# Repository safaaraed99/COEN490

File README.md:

# COEN490 Hardware
This repository contains the PCB design files and AVR microcontroller firmware.

# Firmware contribution
First, install [Microchip Studio](https://www.microchip.com/en-us/tools-resources/develop/microchip-studio) (AKA Atmel Studio).

Next, create a new branch for the feature you want to add. Open up the solution under avr_firmware, make the modifications, commit and push to your branch. Then open up a PR and wait for a review before merging.

See `docs/main.md` for documentation links and programming guides.

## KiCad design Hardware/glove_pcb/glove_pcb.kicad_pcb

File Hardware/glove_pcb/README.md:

Hardware design for the project's PCB

1. Download [Kicad](https://www.kicad.org/) and open `glove_pcb.kicad_pro`
2. Modify schematic in `glove_pcb.kicad_sch`
3. Modify PCB layout in `glove_pcb.kicad_pcb`

TODO write more here!!

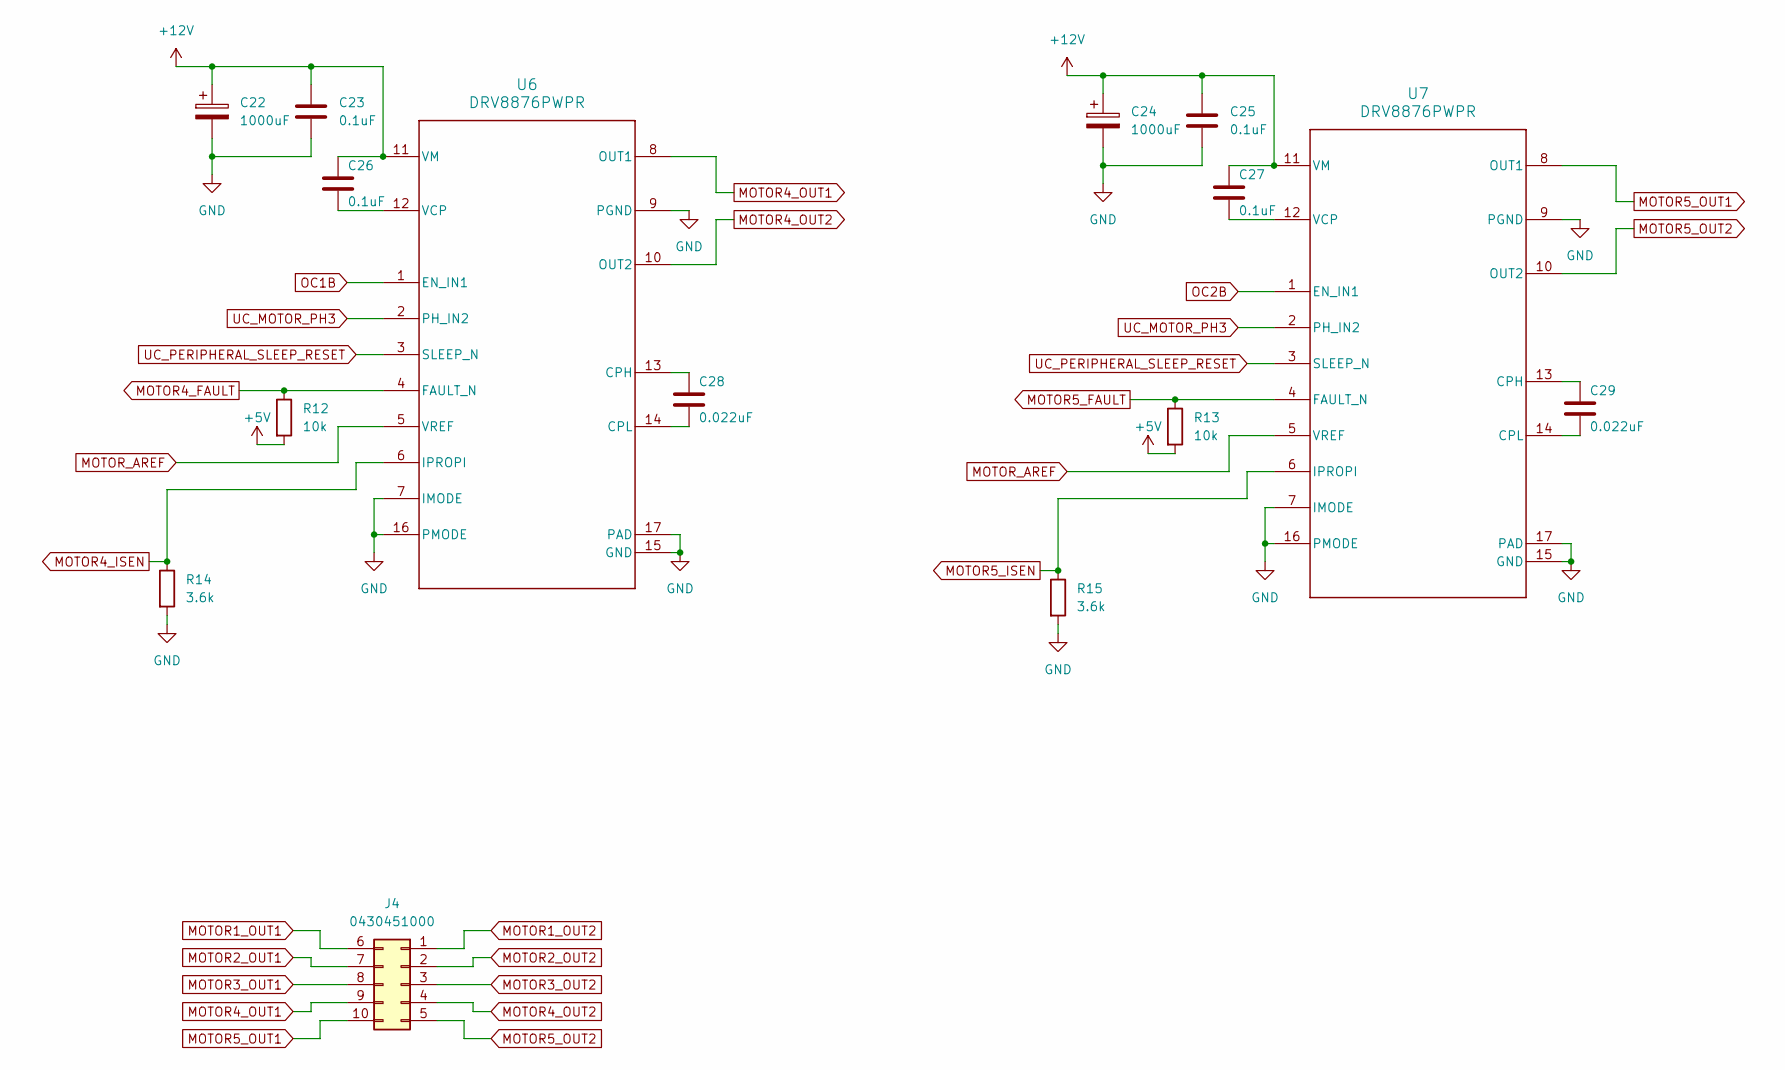
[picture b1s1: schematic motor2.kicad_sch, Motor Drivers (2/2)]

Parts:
C22, C24: 1000uF; CP_Radial_D10.0mm_P5.00mm
C23, C25, C26, C27: 0.1uF; C_0603_1608Metric_Pad1.08x0.95mm_HandSolder
C28, C29: 0.022uF; C_0603_1608Metric_Pad1.08x0.95mm_HandSolder
J4: 0430451000; Molex_Micro-Fit_3.0_43045-1000_2x05_P3.00mm_Horizontal
R12, R13: 10k; R_0805_2012Metric_Pad1.20x1.40mm_HandSolder
R14, R15: 3.6k; R_0805_2012Metric_Pad1.20x1.40mm_HandSolder
U6, U7: DRV8876PWPR; PWP0016J_N

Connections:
+5V: R12.2, R13.2; also elsewhere on the board
+12V: C22.1, C23.1, C24.1, C25.1, C26.1, C27.1, U6.11 (VM), U7.11 (VM); also elsewhere on the board
GND: C22.2, C23.2, C24.2, C25.2, R14.2, R15.2, U6.7 (IMODE), U6.9 (PGND), U6.15 (GND), U6.16 (PMODE), U6.17 (PAD), U7.7 (IMODE), U7.9 (PGND), U7.15 (GND), U7.16 (PMODE), U7.17 (PAD); also elsewhere on the board
MOTOR1_OUT1: J4.6; also elsewhere on the board
MOTOR1_OUT2: J4.1; also elsewhere on the board
MOTOR2_OUT1: J4.7; also elsewhere on the board
MOTOR2_OUT2: J4.2; also elsewhere on the board
MOTOR3_OUT1: J4.8; also elsewhere on the board
MOTOR3_OUT2: J4.3; also elsewhere on the board
MOTOR4_FAULT: R12.1, U6.4 (FAULT_N); also elsewhere on the board
MOTOR4_ISEN: R14.1, U6.6 (IPROPI); also elsewhere on the board
MOTOR4_OUT1: J4.9, U6.8 (OUT1)
MOTOR4_OUT2: J4.4, U6.10 (OUT2)
MOTOR5_FAULT: R13.1, U7.4 (FAULT_N); also elsewhere on the board
MOTOR5_ISEN: R15.1, U7.6 (IPROPI); also elsewhere on the board
MOTOR5_OUT1: J4.10, U7.8 (OUT1)
MOTOR5_OUT2: J4.5, U7.10 (OUT2)
MOTOR_AREF: U6.5 (VREF), U7.5 (VREF); also elsewhere on the board
unnamed: C28.1, U6.13 (CPH)
unnamed: C28.2, U6.14 (CPL)
unnamed: C26.2, U6.12 (VCP)
unnamed: C29.1, U7.13 (CPH)
unnamed: C29.2, U7.14 (CPL)
unnamed: C27.2, U7.12 (VCP)
OC1B: U6.1 (EN_IN1); also elsewhere on the board
OC2B: U7.1 (EN_IN1); also elsewhere on the board
UC_MOTOR_PH3: U6.2 (PH_IN2), U7.2 (PH_IN2); also elsewhere on the board
UC_PERIPHERAL_SLEEP_RESET: U6.3 (SLEEP_N), U7.3 (SLEEP_N); also elsewhere on the board

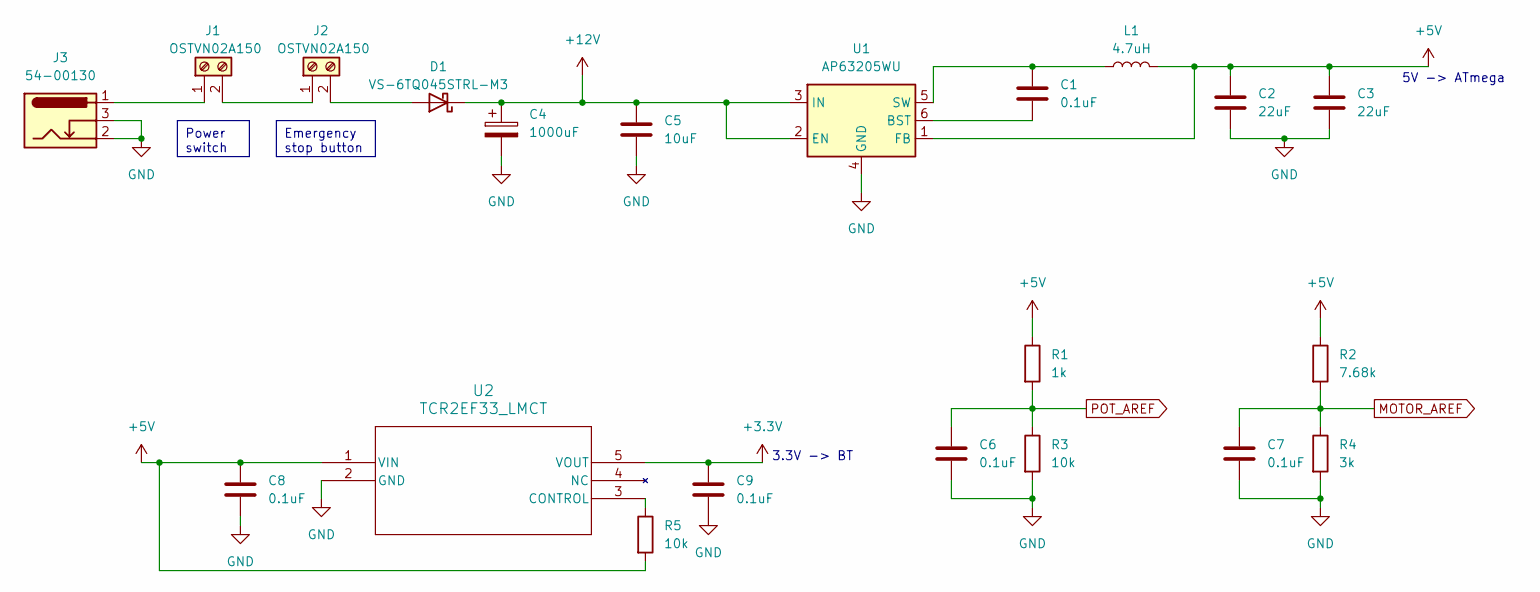
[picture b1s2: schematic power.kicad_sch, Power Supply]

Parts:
C1, C6, C7, C8, C9: 0.1uF; C_0603_1608Metric_Pad1.08x0.95mm_HandSolder
C2, C3: 22uF; C_0805_2012Metric_Pad1.18x1.45mm_HandSolder
C4: 1000uF; CP_Radial_D10.0mm_P5.00mm
C5: 10uF; C_1206_3216Metric_Pad1.33x1.80mm_HandSolder
D1: VS-6TQ045STRL-M3; TO-263-3_TabPin2
J1, J2: OSTVN02A150; TerminalBlock_OnShore_OSTVN02A150_P2.54mm
J3: 54-00130; BarrelJack_Horizontal
L1: 4.7uH; L_7.6x7.6_H3.5
R1: 1k; R_0805_2012Metric_Pad1.20x1.40mm_HandSolder
R2: 7.68k; R_1206_3216Metric_Pad1.30x1.75mm_HandSolder
R3, R5: 10k; R_0805_2012Metric_Pad1.20x1.40mm_HandSolder
R4: 3k; R_0805_2012Metric_Pad1.20x1.40mm_HandSolder
U1: AP63205WU; TSOT-23-6
U2: TCR2EF33_LMCT; SOT-25 SMV_TOS

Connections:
+3.3V: C9.1, U2.5 (VOUT); also elsewhere on the board
+5V: C2.1, C3.1, C8.1, L1.2, R1.1, R2.1, R5.2, U1.1 (FB), U2.1 (VIN); also elsewhere on the board
+12V: C4.1, C5.1, D1.2 (K), U1.2 (EN), U1.3 (IN); also elsewhere on the board
GND: C2.2, C3.2, C4.2, C5.2, C6.2, C7.2, C8.2, C9.2, J3.2, J3.3, R3.2, R4.2, U1.4 (GND), U2.2 (GND); also elsewhere on the board
MOTOR_AREF: C7.1, R2.2, R4.1; also elsewhere on the board
unnamed: D1.3 (A), J2.2
unnamed: J1.1, J3.1
unnamed: J1.2, J2.1
unnamed: C1.2, U1.6 (BST)
unnamed: C1.1, L1.1, U1.5 (SW)
unnamed: R5.1, U2.3 (CONTROL)
POT_AREF: C6.1, R1.2, R3.1; also elsewhere on the board

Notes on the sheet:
Power switch
Emergency stop button
5V -> ATmega
3.3V -> BT

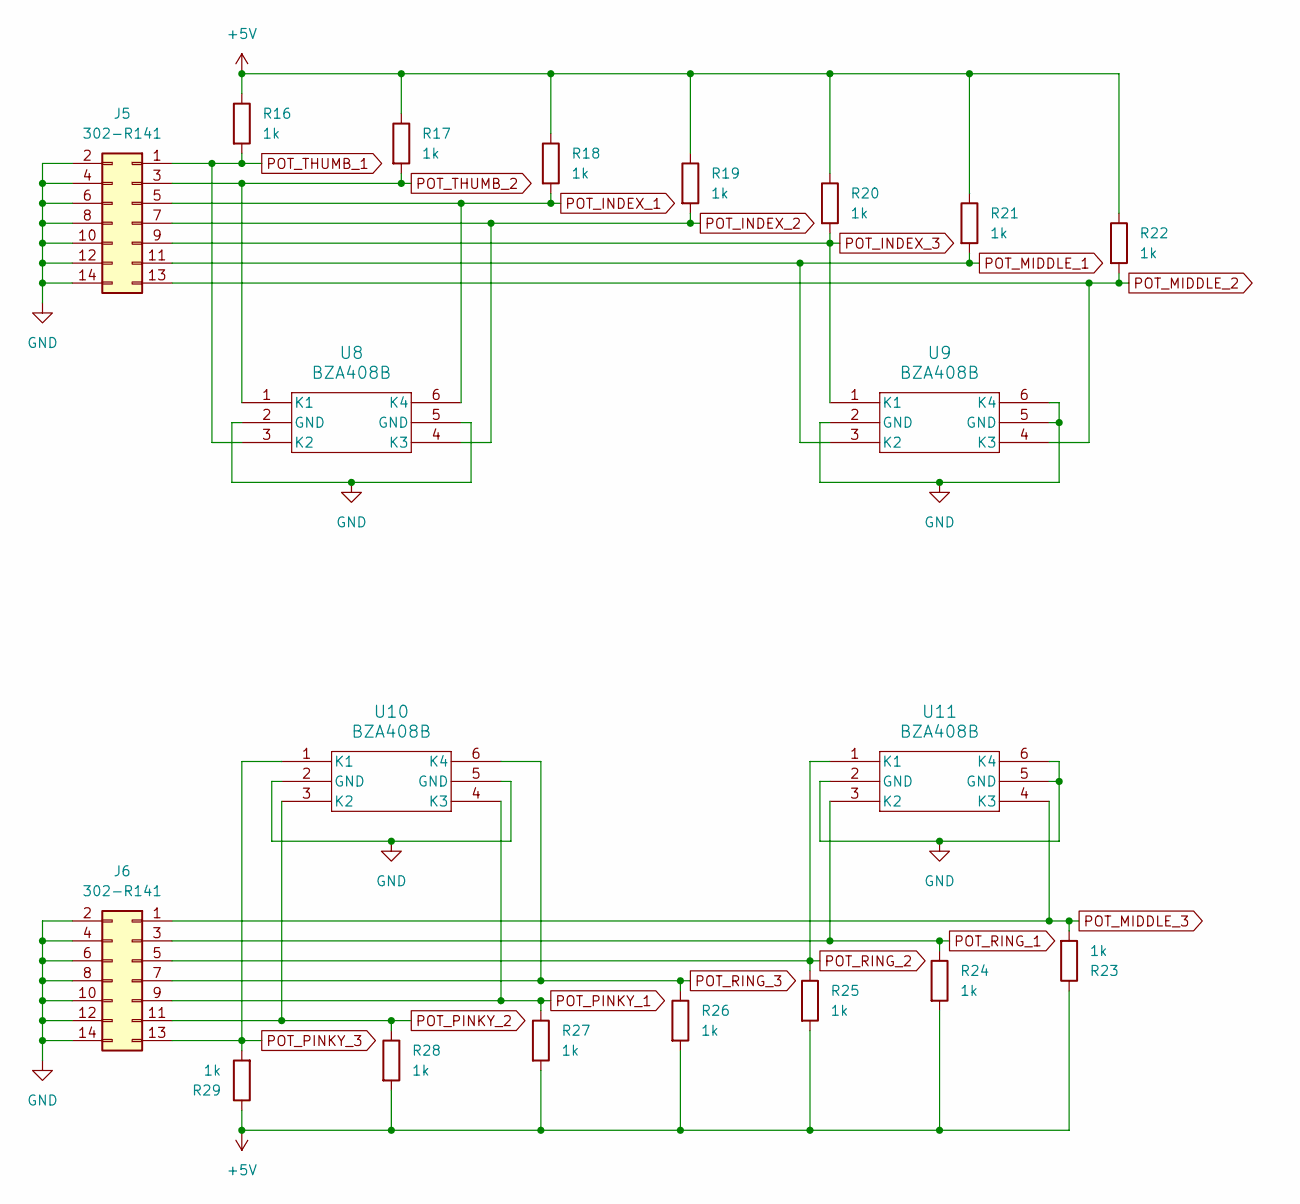
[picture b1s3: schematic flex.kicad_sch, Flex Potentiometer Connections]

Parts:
J5, J6: 302-R141; PinSocket_2x07_P2.54mm_Horizontal_302-R141
R16, R17, R18, R19, R20, R21, R22, R23, R24, R25, R26, R27, R28, R29: 1k; R_0805_2012Metric_Pad1.20x1.40mm_HandSolder
U8, U9, U10, U11: BZA408B; SOT457_NXP

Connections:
+5V: R16.1, R17.1, R18.1, R19.1, R20.1, R21.1, R22.1, R23.1, R24.2, R25.2, R26.2, R27.2, R28.2, R29.1; also elsewhere on the board
GND: J5.2, J5.4, J5.6, J5.8, J5.10, J5.12, J5.14, J6.2, J6.4, J6.6, J6.8, J6.10, J6.12, J6.14, U8.2 (GND), U8.5 (GND), U9.2 (GND), U9.5 (GND), U9.6 (K4), U10.2 (GND), U10.5 (GND), U11.2 (GND), U11.5 (GND), U11.6 (K4); also elsewhere on the board
POT_INDEX_1: J5.5, R18.2, U8.6 (K4); also elsewhere on the board
POT_INDEX_2: J5.7, R19.2, U8.4 (K3); also elsewhere on the board
POT_INDEX_3: J5.9, R20.2, U9.1 (K1); also elsewhere on the board
POT_MIDDLE_1: J5.11, R21.2, U9.3 (K2); also elsewhere on the board
POT_MIDDLE_2: J5.13, R22.2, U9.4 (K3); also elsewhere on the board
POT_MIDDLE_3: J6.1, R23.2, U11.4 (K3); also elsewhere on the board
POT_PINKY_1: J6.9, R27.1, U10.4 (K3); also elsewhere on the board
POT_PINKY_2: J6.11, R28.1, U10.3 (K2); also elsewhere on the board
POT_PINKY_3: J6.13, R29.2, U10.1 (K1); also elsewhere on the board
POT_RING_1: J6.3, R24.1, U11.3 (K2); also elsewhere on the board
POT_RING_2: J6.5, R25.1, U11.1 (K1); also elsewhere on the board
POT_RING_3: J6.7, R26.1, U10.6 (K4); also elsewhere on the board
POT_THUMB_1: J5.1, R16.2, U8.3 (K2); also elsewhere on the board
POT_THUMB_2: J5.3, R17.2, U8.1 (K1); also elsewhere on the board

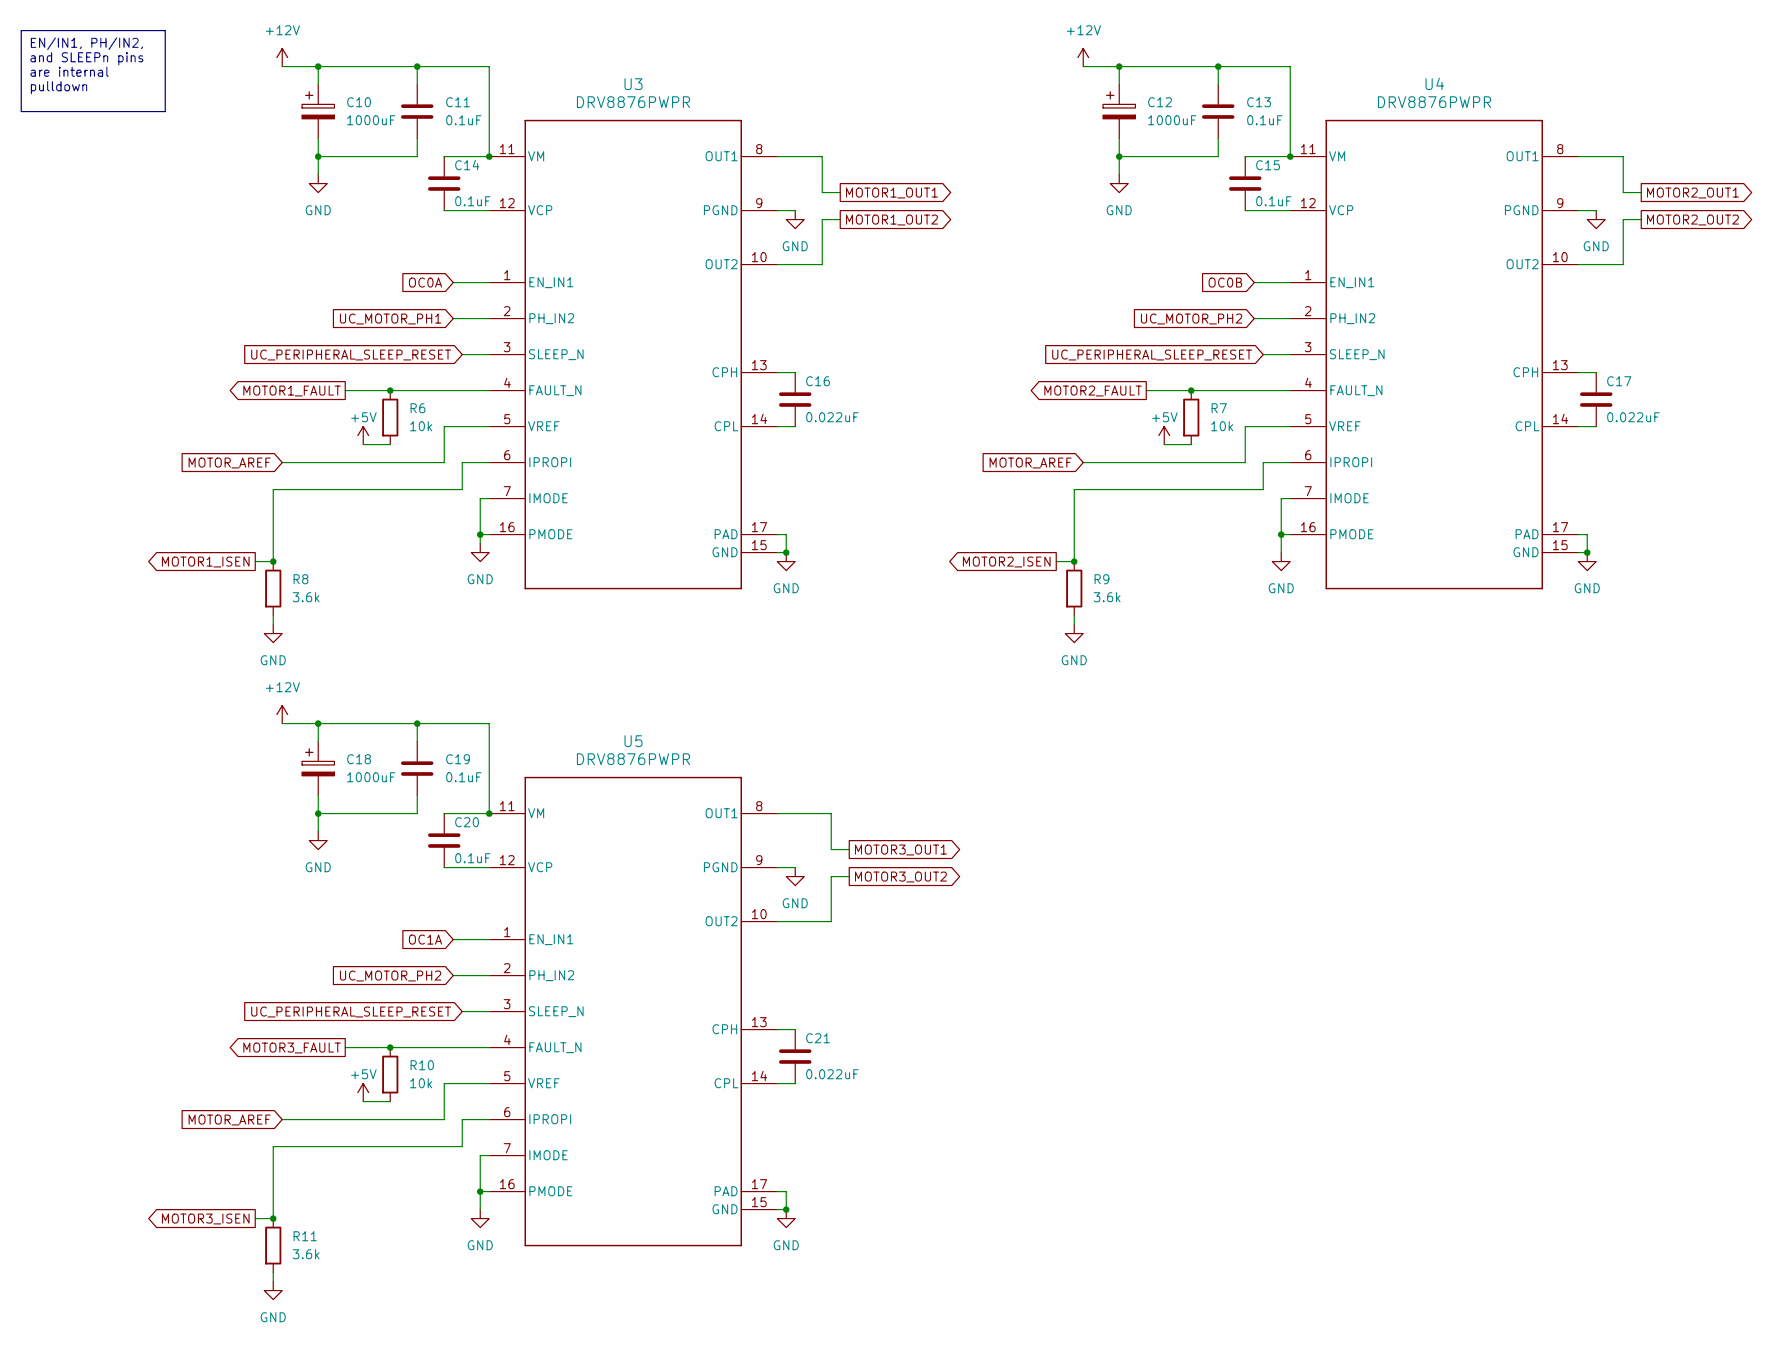
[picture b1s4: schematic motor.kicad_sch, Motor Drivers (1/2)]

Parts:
C10, C12, C18: 1000uF; CP_Radial_D10.0mm_P5.00mm
C11, C13, C14, C15, C19, C20: 0.1uF; C_0603_1608Metric_Pad1.08x0.95mm_HandSolder
C16, C17, C21: 0.022uF; C_0603_1608Metric_Pad1.08x0.95mm_HandSolder
R6, R7, R10: 10k; R_0805_2012Metric_Pad1.20x1.40mm_HandSolder
R8, R9, R11: 3.6k; R_0805_2012Metric_Pad1.20x1.40mm_HandSolder
U3, U4, U5: DRV8876PWPR; PWP0016J_N

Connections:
+5V: R6.2, R7.2, R10.2; also elsewhere on the board
+12V: C10.1, C11.1, C12.1, C13.1, C14.1, C15.1, C18.1, C19.1, C20.1, U3.11 (VM), U4.11 (VM), U5.11 (VM); also elsewhere on the board
GND: C10.2, C11.2, C12.2, C13.2, C18.2, C19.2, R8.2, R9.2, R11.2, U3.7 (IMODE), U3.9 (PGND), U3.15 (GND), U3.16 (PMODE), U3.17 (PAD), U4.7 (IMODE), U4.9 (PGND), U4.15 (GND), U4.16 (PMODE), U4.17 (PAD), U5.7 (IMODE), U5.9 (PGND), U5.15 (GND), U5.16 (PMODE), U5.17 (PAD); also elsewhere on the board
MOTOR1_FAULT: R6.1, U3.4 (FAULT_N); also elsewhere on the board
MOTOR1_ISEN: R8.1, U3.6 (IPROPI); also elsewhere on the board
MOTOR1_OUT1: U3.8 (OUT1); also elsewhere on the board
MOTOR1_OUT2: U3.10 (OUT2); also elsewhere on the board
MOTOR2_FAULT: R7.1, U4.4 (FAULT_N); also elsewhere on the board
MOTOR2_ISEN: R9.1, U4.6 (IPROPI); also elsewhere on the board
MOTOR2_OUT1: U4.8 (OUT1); also elsewhere on the board
MOTOR2_OUT2: U4.10 (OUT2); also elsewhere on the board
MOTOR3_FAULT: R10.1, U5.4 (FAULT_N); also elsewhere on the board
MOTOR3_ISEN: R11.1, U5.6 (IPROPI); also elsewhere on the board
MOTOR3_OUT1: U5.8 (OUT1); also elsewhere on the board
MOTOR3_OUT2: U5.10 (OUT2); also elsewhere on the board
MOTOR_AREF: U3.5 (VREF), U4.5 (VREF), U5.5 (VREF); also elsewhere on the board
unnamed: C16.1, U3.13 (CPH)
unnamed: C16.2, U3.14 (CPL)
unnamed: C14.2, U3.12 (VCP)
unnamed: C17.1, U4.13 (CPH)
unnamed: C17.2, U4.14 (CPL)
unnamed: C15.2, U4.12 (VCP)
unnamed: C21.1, U5.13 (CPH)
unnamed: C21.2, U5.14 (CPL)
unnamed: C20.2, U5.12 (VCP)
OC0A: U3.1 (EN_IN1); also elsewhere on the board
OC0B: U4.1 (EN_IN1); also elsewhere on the board
OC1A: U5.1 (EN_IN1); also elsewhere on the board
UC_MOTOR_PH1: U3.2 (PH_IN2); also elsewhere on the board
UC_MOTOR_PH2: U4.2 (PH_IN2), U5.2 (PH_IN2); also elsewhere on the board
UC_PERIPHERAL_SLEEP_RESET: U3.3 (SLEEP_N), U4.3 (SLEEP_N), U5.3 (SLEEP_N); also elsewhere on the board

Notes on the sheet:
EN/IN1, PH/IN2, and SLEEPn pins are internal pulldown

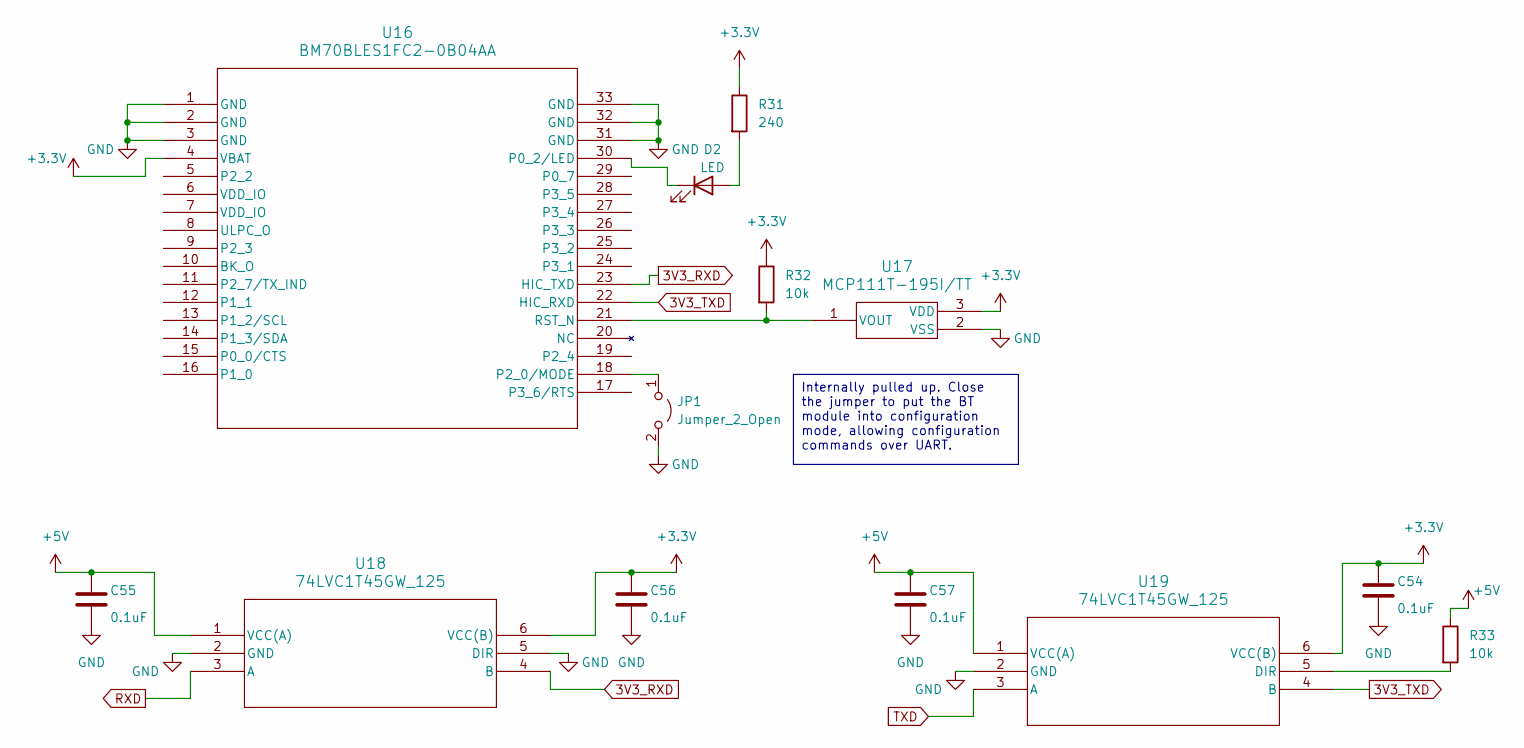
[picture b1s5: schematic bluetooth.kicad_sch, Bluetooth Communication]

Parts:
C54, C55, C56, C57: 0.1uF; C_0603_1608Metric_Pad1.08x0.95mm_HandSolder
D2: LED; LED_D5.0mm
JP1: Jumper_2_Open; PinHeader_1x02_P2.54mm_Vertical
R31: 240; R_0805_2012Metric_Pad1.20x1.40mm_HandSolder
R32, R33: 10k; R_0805_2012Metric_Pad1.20x1.40mm_HandSolder
U16: BM70BLES1FC2-0B04AA; BM70BLES1FC2_MCH(2)
U17: MCP111T-195I/TT; SOT-23_MC_MCH
U18, U19: 74LVC1T45GW_125; TSSOP6_SOT363-2_NEX

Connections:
3V3_RXD: U16.23 (HIC_TXD), U18.4 (B)
3V3_TXD: U16.22 (HIC_RXD), U19.4 (B)
+3.3V: C54.1, C56.1, R31.1, R32.1, U16.4 (VBAT), U17.3 (VDD), U18.6 (VCC(B)), U19.6 (VCC(B)); also elsewhere on the board
+5V: C55.1, C57.1, R33.1, U18.1 (VCC(A)), U19.1 (VCC(A)); also elsewhere on the board
GND: C54.2, C55.2, C56.2, C57.2, JP1.2 (B), U16.1 (GND), U16.2 (GND), U16.3 (GND), U16.31 (GND), U16.32 (GND), U16.33 (GND), U17.2 (VSS), U18.2 (GND), U18.5 (DIR), U19.2 (GND); also elsewhere on the board
unnamed: D2.2 (A), R31.2
unnamed: D2.1 (K), U16.30 (P0_2/LED)
unnamed: JP1.1 (A), U16.18 (P2_0/MODE)
unnamed: R32.2, U16.21 (RST_N), U17.1 (VOUT)
unnamed: R33.2, U19.5 (DIR)
RXD: U18.3 (A); also elsewhere on the board
TXD: U19.3 (A); also elsewhere on the board

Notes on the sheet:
Internally pulled up. Close the jumper to put the BT module into configuration mode, allowing configuration commands over UART.

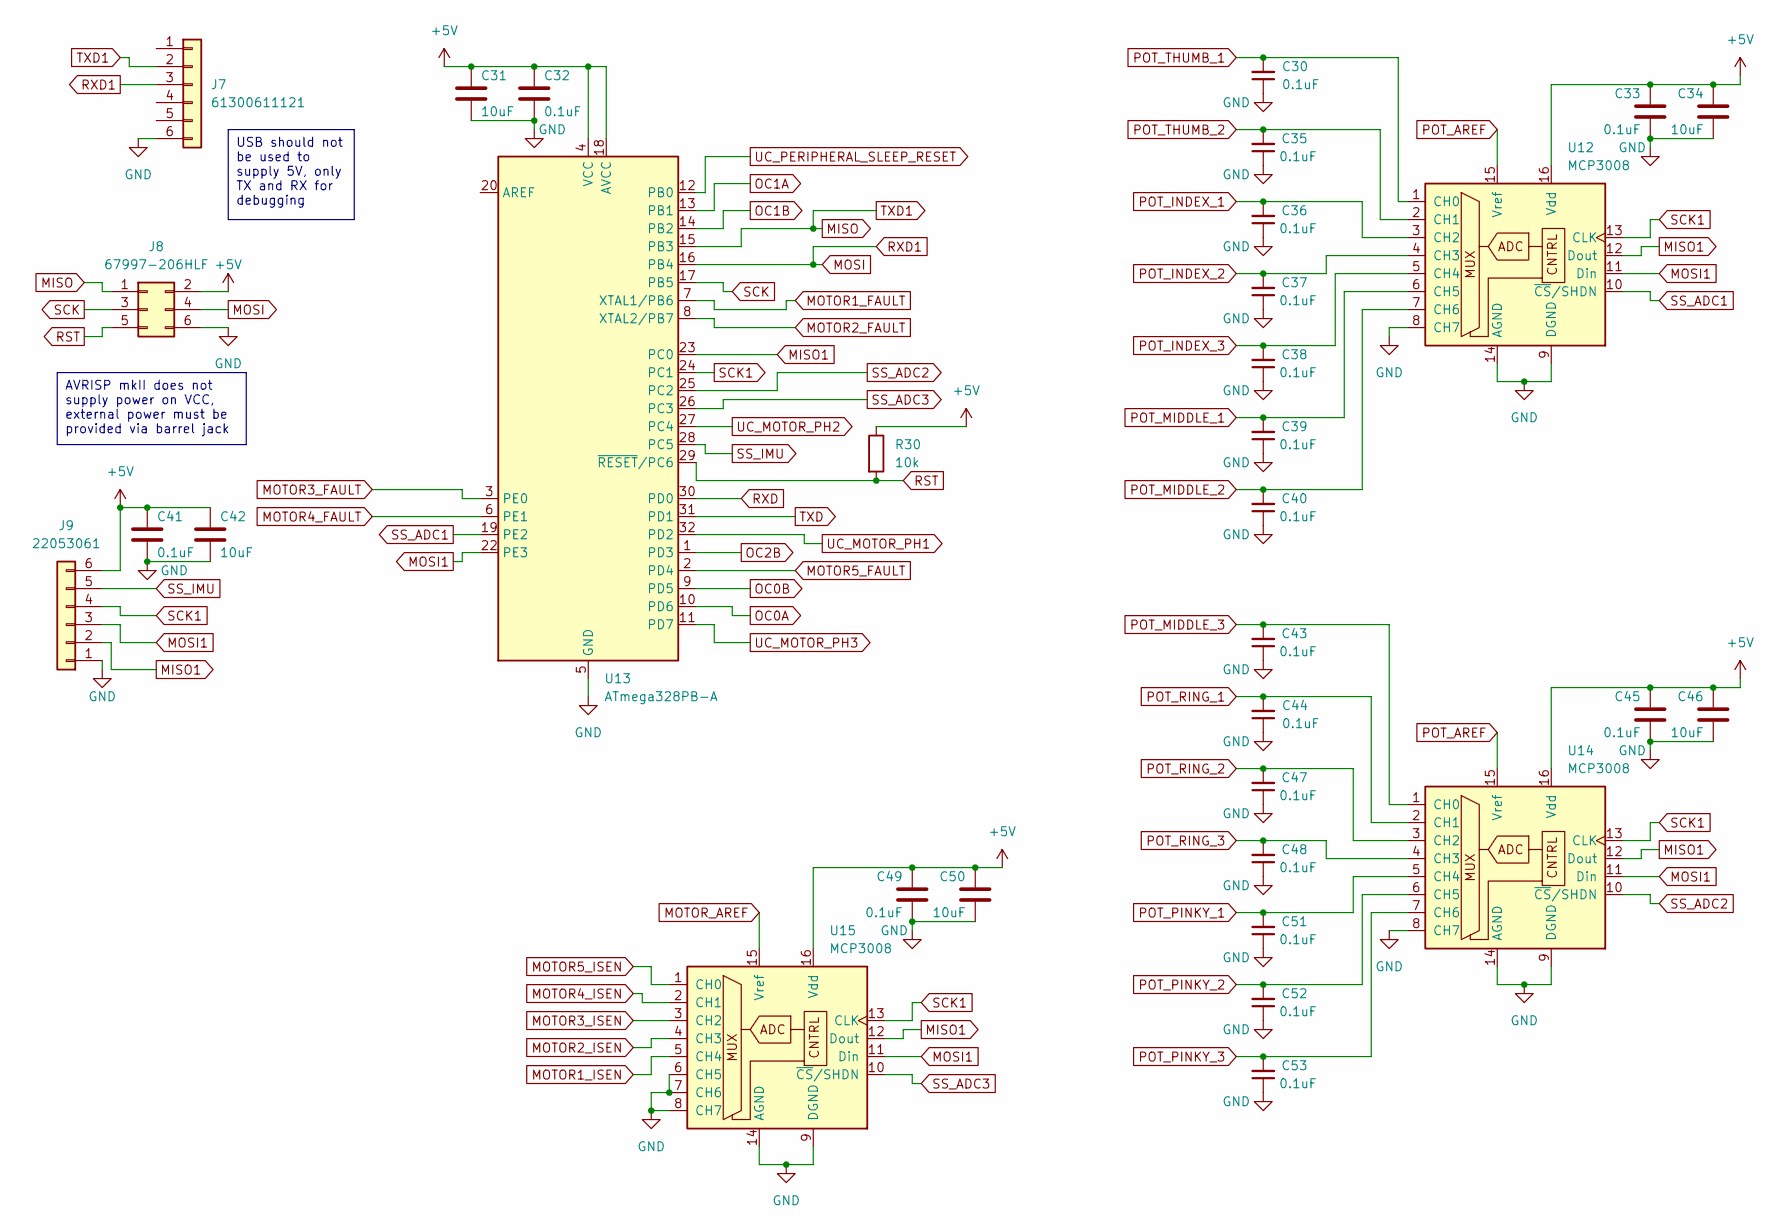
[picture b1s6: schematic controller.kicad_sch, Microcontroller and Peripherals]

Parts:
C30, C32, C33, C35, C36, C37, C38, C39, C40, C41, C43, C44, C45, C47, C48, C49, C51, C52, C53: 0.1uF; C_0603_1608Metric_Pad1.08x0.95mm_HandSolder
C31, C34, C42, C46, C50: 10uF; C_1206_3216Metric_Pad1.33x1.80mm_HandSolder
J7: 61300611121; PinSocket_1x06_P2.54mm_Vertical
J8: 67997-206HLF; PinHeader_2x03_P2.54mm_Vertical
J9: 22053061; PinSocket_1x06_P2.54mm_Horizontal
R30: 10k; R_0805_2012Metric_Pad1.20x1.40mm_HandSolder
U12, U14, U15: MCP3008; SOIC-16_3.9x9.9mm_P1.27mm
U13: ATmega328PB-A; TQFP-32_7x7mm_P0.8mm

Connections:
+5V: C31.1, C32.1, C33.1, C34.1, C41.1, C42.1, C45.1, C46.1, C49.1, C50.1, J8.2, J9.6, R30.1, U12.16 (Vdd), U13.4 (VCC), U13.18 (AVCC), U14.16 (Vdd), U15.16 (Vdd); also elsewhere on the board
GND: C30.1, C31.2, C32.2, C33.2, C34.2, C35.1, C36.1, C37.1, C38.1, C39.1, C40.1, C41.2, C42.2, C43.1, C44.1, C45.2, C46.2, C47.1, C48.1, C49.2, C50.2, C51.1, C52.1, C53.1, J7.6, J8.6, J9.1, U12.8 (CH7), U12.9 (DGND), U12.14 (AGND), U13.5 (GND), U13.21 (GND), U14.8 (CH7), U14.9 (DGND), U14.14 (AGND), U15.6 (CH5), U15.7 (CH6), U15.8 (CH7), U15.9 (DGND), U15.14 (AGND); also elsewhere on the board
MISO: J7.2, J8.1, U13.15 (PB3)
MISO1: J9.2, U12.12 (Dout), U13.23 (PC0), U14.12 (Dout), U15.12 (Dout)
MOSI: J7.3, J8.4, U13.16 (PB4)
MOSI1: J9.3, U12.11 (Din), U13.22 (PE3), U14.11 (Din), U15.11 (Din)
MOTOR1_FAULT: U13.7 (XTAL1/PB6); also elsewhere on the board
MOTOR1_ISEN: U15.5 (CH4); also elsewhere on the board
MOTOR2_FAULT: U13.8 (XTAL2/PB7); also elsewhere on the board
MOTOR2_ISEN: U15.4 (CH3); also elsewhere on the board
MOTOR3_FAULT: U13.3 (PE0); also elsewhere on the board
MOTOR3_ISEN: U15.3 (CH2); also elsewhere on the board
MOTOR4_FAULT: U13.6 (PE1); also elsewhere on the board
MOTOR4_ISEN: U15.2 (CH1); also elsewhere on the board
MOTOR5_FAULT: U13.2 (PD4); also elsewhere on the board
MOTOR5_ISEN: U15.1 (CH0); also elsewhere on the board
MOTOR_AREF: U15.15 (Vref); also elsewhere on the board
OC0A: U13.10 (PD6); also elsewhere on the board
OC0B: U13.9 (PD5); also elsewhere on the board
OC1A: U13.13 (PB1); also elsewhere on the board
OC1B: U13.14 (PB2); also elsewhere on the board
OC2B: U13.1 (PD3); also elsewhere on the board
POT_AREF: U12.15 (Vref), U14.15 (Vref); also elsewhere on the board
POT_INDEX_1: C36.2, U12.3 (CH2); also elsewhere on the board
POT_INDEX_2: C37.2, U12.4 (CH3); also elsewhere on the board
POT_INDEX_3: C38.2, U12.5 (CH4); also elsewhere on the board
POT_MIDDLE_1: C39.2, U12.6 (CH5); also elsewhere on the board
POT_MIDDLE_2: C40.2, U12.7 (CH6); also elsewhere on the board
POT_MIDDLE_3: C43.2, U14.1 (CH0); also elsewhere on the board
POT_PINKY_1: C51.2, U14.5 (CH4); also elsewhere on the board
POT_PINKY_2: C52.2, U14.6 (CH5); also elsewhere on the board
POT_PINKY_3: C53.2, U14.7 (CH6); also elsewhere on the board
POT_RING_1: C44.2, U14.2 (CH1); also elsewhere on the board
POT_RING_2: C47.2, U14.3 (CH2); also elsewhere on the board
POT_RING_3: C48.2, U14.4 (CH3); also elsewhere on the board
POT_THUMB_1: C30.2, U12.1 (CH0); also elsewhere on the board
POT_THUMB_2: C35.2, U12.2 (CH1); also elsewhere on the board
RST: J8.5, R30.2, U13.29 (~RESET/PC6)
RXD: U13.30 (PD0); also elsewhere on the board
SCK: J8.3, U13.17 (PB5)
SCK1: J9.4, U12.13 (CLK), U13.24 (PC1), U14.13 (CLK), U15.13 (CLK)
SS_ADC1: U12.10 (~CS/SHDN), U13.19 (PE2)
SS_ADC2: U13.25 (PC2), U14.10 (~CS/SHDN)
SS_ADC3: U13.26 (PC3), U15.10 (~CS/SHDN)
SS_IMU: J9.5, U13.28 (PC5)
TXD: U13.31 (PD1); also elsewhere on the board
UC_MOTOR_PH1: U13.32 (PD2); also elsewhere on the board
UC_MOTOR_PH2: U13.27 (PC4); also elsewhere on the board
UC_MOTOR_PH3: U13.11 (PD7); also elsewhere on the board
UC_PERIPHERAL_SLEEP_RESET: U13.12 (PB0); also elsewhere on the board

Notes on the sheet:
USB should not be used to supply 5V, only TX and RX for debugging
AVRISP mkII does not supply power on VCC, external power must be provided via barrel jack

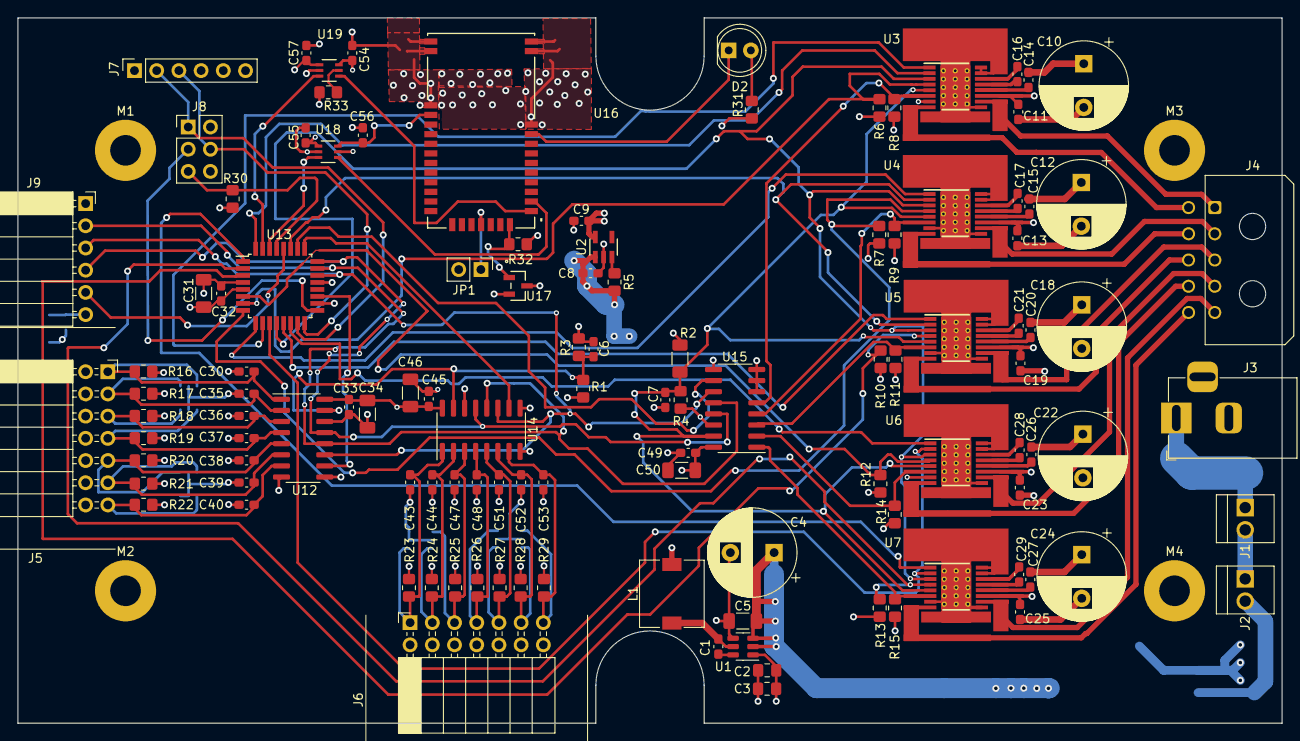
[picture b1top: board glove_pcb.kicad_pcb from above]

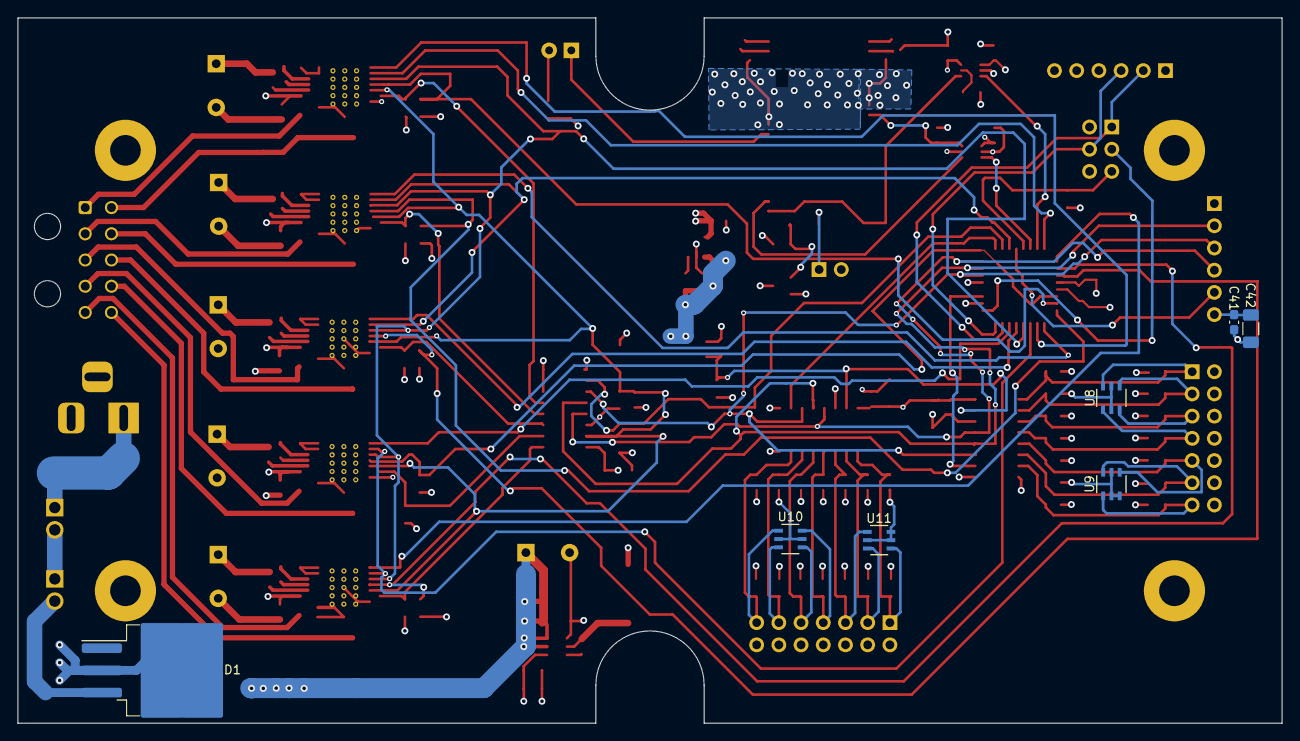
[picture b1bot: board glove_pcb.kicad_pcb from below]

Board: 4 copper layers, 144.6 x 80.7 mm, 126 parts (7 on the bottom side), 90 nets.

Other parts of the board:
M1, M2, M3, M4: MountingHole_3.5mm_Pad

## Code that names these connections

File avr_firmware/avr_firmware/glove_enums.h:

/*
 * glove_enums.h
 *
 * Created: 2024-03-19 1:57:33 PM
 *  Author: Matthew Faigan
 */ 


#ifndef GLOVE_ENUMS_H_
#define GLOVE_ENUMS_H_

typedef enum
{
	POT_THUMB_1 = 0,
	POT_THUMB_2 = 1,
	POT_INDEX_1 = 2,
	POT_INDEX_2 = 3,
	POT_INDEX_3 = 4,
	POT_MIDDLE_1 = 5,
	POT_MIDDLE_2 = 6,
	POT_MIDDLE_3 = 7,
	POT_RING_1 = 8,
	POT_RING_2 = 9,
	POT_RING_3 = 10,
	POT_PINKY_1 = 11,
	POT_PINKY_2 = 12,
	POT_PINKY_3 = 13
} potentiometer;

// N.B. The motor channels were connected in reverse order to make the PCB layout easier
typedef enum
{
	MOTOR_PINKY = 0,
	MOTOR_RING = 1,
	MOTOR_MIDDLE = 2,
	MOTOR_INDEX = 3,
	MOTOR_THUMB = 4
} motor;

typedef enum
{
	DIRECTION_FORWARD,
	DIRECTION_BACKWARD
} motor_direction;

#endif /* GLOVE_ENUMS_H_ */

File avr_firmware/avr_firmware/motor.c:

/*
 * motor.c
 *
 * Created: 2024-03-19 1:37:31 PM
 *  Author: Matthew Faigan
 */ 

#include "motor.h"

#include <avr/io.h>
#include <avr/interrupt.h>
#include <stdbool.h>

#include "uart.h"

// ISR will set this so we can handle notifying the application in the main loop
volatile bool motor_faulted[MOTOR_COUNT];

void setup_motors(void)
{
	// N.B. The different hardware counters have different capabilities and configuration methods.
	// Before you modify any of the setup code here, make sure you read the appropriate section in the datasheet.
	
	/* TC0 (thumb and index finger) */
	// Set PD5 and PD6 as outputs
	DDRD |= (1<<DDD6) | (1<<DDD5);
	// Set OC0A and OC0B to fast PWM, non-inverting
	TCCR0A = (1<<COM0A1) | (1<<COM0B1) | (1<<WGM01) | (1<<WGM00);
	// Set no prescaling
	TCCR0B = (1<<CS00);
	// Default both output compares to 0
	OCR0A = 0;
	OCR0B = 0;
	
	/* TC1 (middle and ring fingers) */
	// Set PB1 and PB2 as outputs
	DDRB |= (1<<DDB2) | (1<<DDB1);
	// Set fast PWM non-inverting with top value of 0x00FF, no prescaling
	TCCR1A = (1<<COM1A1) | (1<<COM1B1) | (1<<WGM10);
	TCCR1B = (1<<WGM12) | (1<<CS10);
	// Default output compares to 0
	OCR1A = 0;
	OCR1B = 0;
	
	/* TC2 (pinky) */
	// Set PD3 as output
	DDRD |= (1<<DDD3);
	// Leave OC2A unused, set OC2B to fast PWM non-inverting
	TCCR2A = (1<<COM2B1) | (1<<WGM21) | (1<<WGM20);
	// No prescaling
	TCCR2B = (1<<CS20);
	// Default output compare to 0
	OCR2B = 0;
	
	// Initialize pin change interrupts for motor fault
	PCICR = (1<<PCIE3) | (1<<PCIE2) | (1<<PCIE0);
	PCMSK3 = (1<<PCINT25) | (1<<PCINT24);
	PCMSK2 = (1<<PCINT20);
	PCMSK0 = (1<<PCINT7) | (1<<PCINT6);
}

int set_motor_speed(motor motor_num, uint8_t duty)
{
	switch (motor_num)
	{
		case MOTOR_THUMB:
			OCR0A = duty;
			break;
		case MOTOR_INDEX:
			OCR0B = duty;
			break;
		case MOTOR_MIDDLE:
			OCR1A = duty;
			break;
		case MOTOR_RING:
			OCR1B = duty;
			break;
		case MOTOR_PINKY:
			OCR2B = duty;
			break;
		default:
			return 1;
	}
	return 0;
}

// This is ugly but I don't know a better way to do it!!
int set_motor_phase(motor motor_num, motor_direction direction)
{
	// Get the current value of the register containing the bit to change
	uint8_t current_value;
	uint8_t mask;
	switch (motor_num)
	{
		case MOTOR_THUMB:
			current_value = PORTD;
			mask = 1<<PORTD2;
			break;
		case MOTOR_INDEX:
		case MOTOR_MIDDLE:
			current_value = PORTC;
			mask = 1<<PORTC4;
			break;
		case MOTOR_RING:
		case MOTOR_PINKY:
			current_value = PORTD;
			mask = 1<<PORTD7;
			break;
		default:
			return 1;
	}
	
	// Motor has forward direction if PH = 1, backwards if PH = 0
	uint8_t new_value;
	switch (direction)
	{
		case DIRECTION_FORWARD:
			new_value = current_value | mask;
			break;
		case DIRECTION_BACKWARD:
			new_value = current_value & ~mask;
			break;
		default:
			return 1;
	}
	
	// Set the new value
	switch (motor_num)
	{
		case MOTOR_THUMB:
		case MOTOR_RING:
		case MOTOR_PINKY:
			PORTD = new_value;
			break;
		case MOTOR_INDEX:
		case MOTOR_MIDDLE:
			PORTC = new_value;
			break;
		default:
			return 1;
	}
	return 0;
}

int set_motor_enable(uint8_t state)
{
	if (state != 0 && state != 1)
	{
		return 1;
	}
	
	uint8_t mask = 1<<PORTB0;
	uint8_t new_bit = state<<PORTB0;
	uint8_t current = PORTB;
	
	PORTB = (current & ~mask) | (new_bit & mask);
	
	return 0;
}

ISR(PCINT3_vect)
{
	if (!(PORTE & (1<<PORTE0)))
	{
		set_motor_enable(0);
		motor_faulted[MOTOR_MIDDLE] = true;
	}
	if (!(PORTE & (1<<PORTE1)))
	{
		set_motor_enable(0);
		motor_faulted[MOTOR_RING] = true;
	}
}

ISR(PCINT2_vect)
{
	if (!(PORTD & (1<<PORTD4)))
	{
		set_motor_enable(0);
		motor_faulted[MOTOR_PINKY] = true;
	}
}

ISR(PCINT0_vect)
{
	if (!(PORTB & (1<<PORTB6)))
	{
		set_motor_enable(0);
		motor_faulted[MOTOR_THUMB] = true;
	}
	if (!(PORTB & (1<<PORTB7)))
	{
		set_motor_enable(0);
		motor_faulted[MOTOR_INDEX] = true;
	}
}
